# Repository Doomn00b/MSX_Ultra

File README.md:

# MSX_Ultra
 MSX2+ compatible Mini-ITX computer system, inspired by Sergey Kiselev's Omega Home Computer.

 This project is an open source implementation, and extension, of an MSX2+ compatible computer. The project is modular, and is built using a combination of 1980's-1990's era components - Z380 CPU, V9958 VDP, YM2610 PSG/FM-generator, and some newer components, such as 512 KiB SRAM and 512 KiB Flash ROM and dual FPGA's for the MSX-engine/Chipset (AT40K FPGAs).

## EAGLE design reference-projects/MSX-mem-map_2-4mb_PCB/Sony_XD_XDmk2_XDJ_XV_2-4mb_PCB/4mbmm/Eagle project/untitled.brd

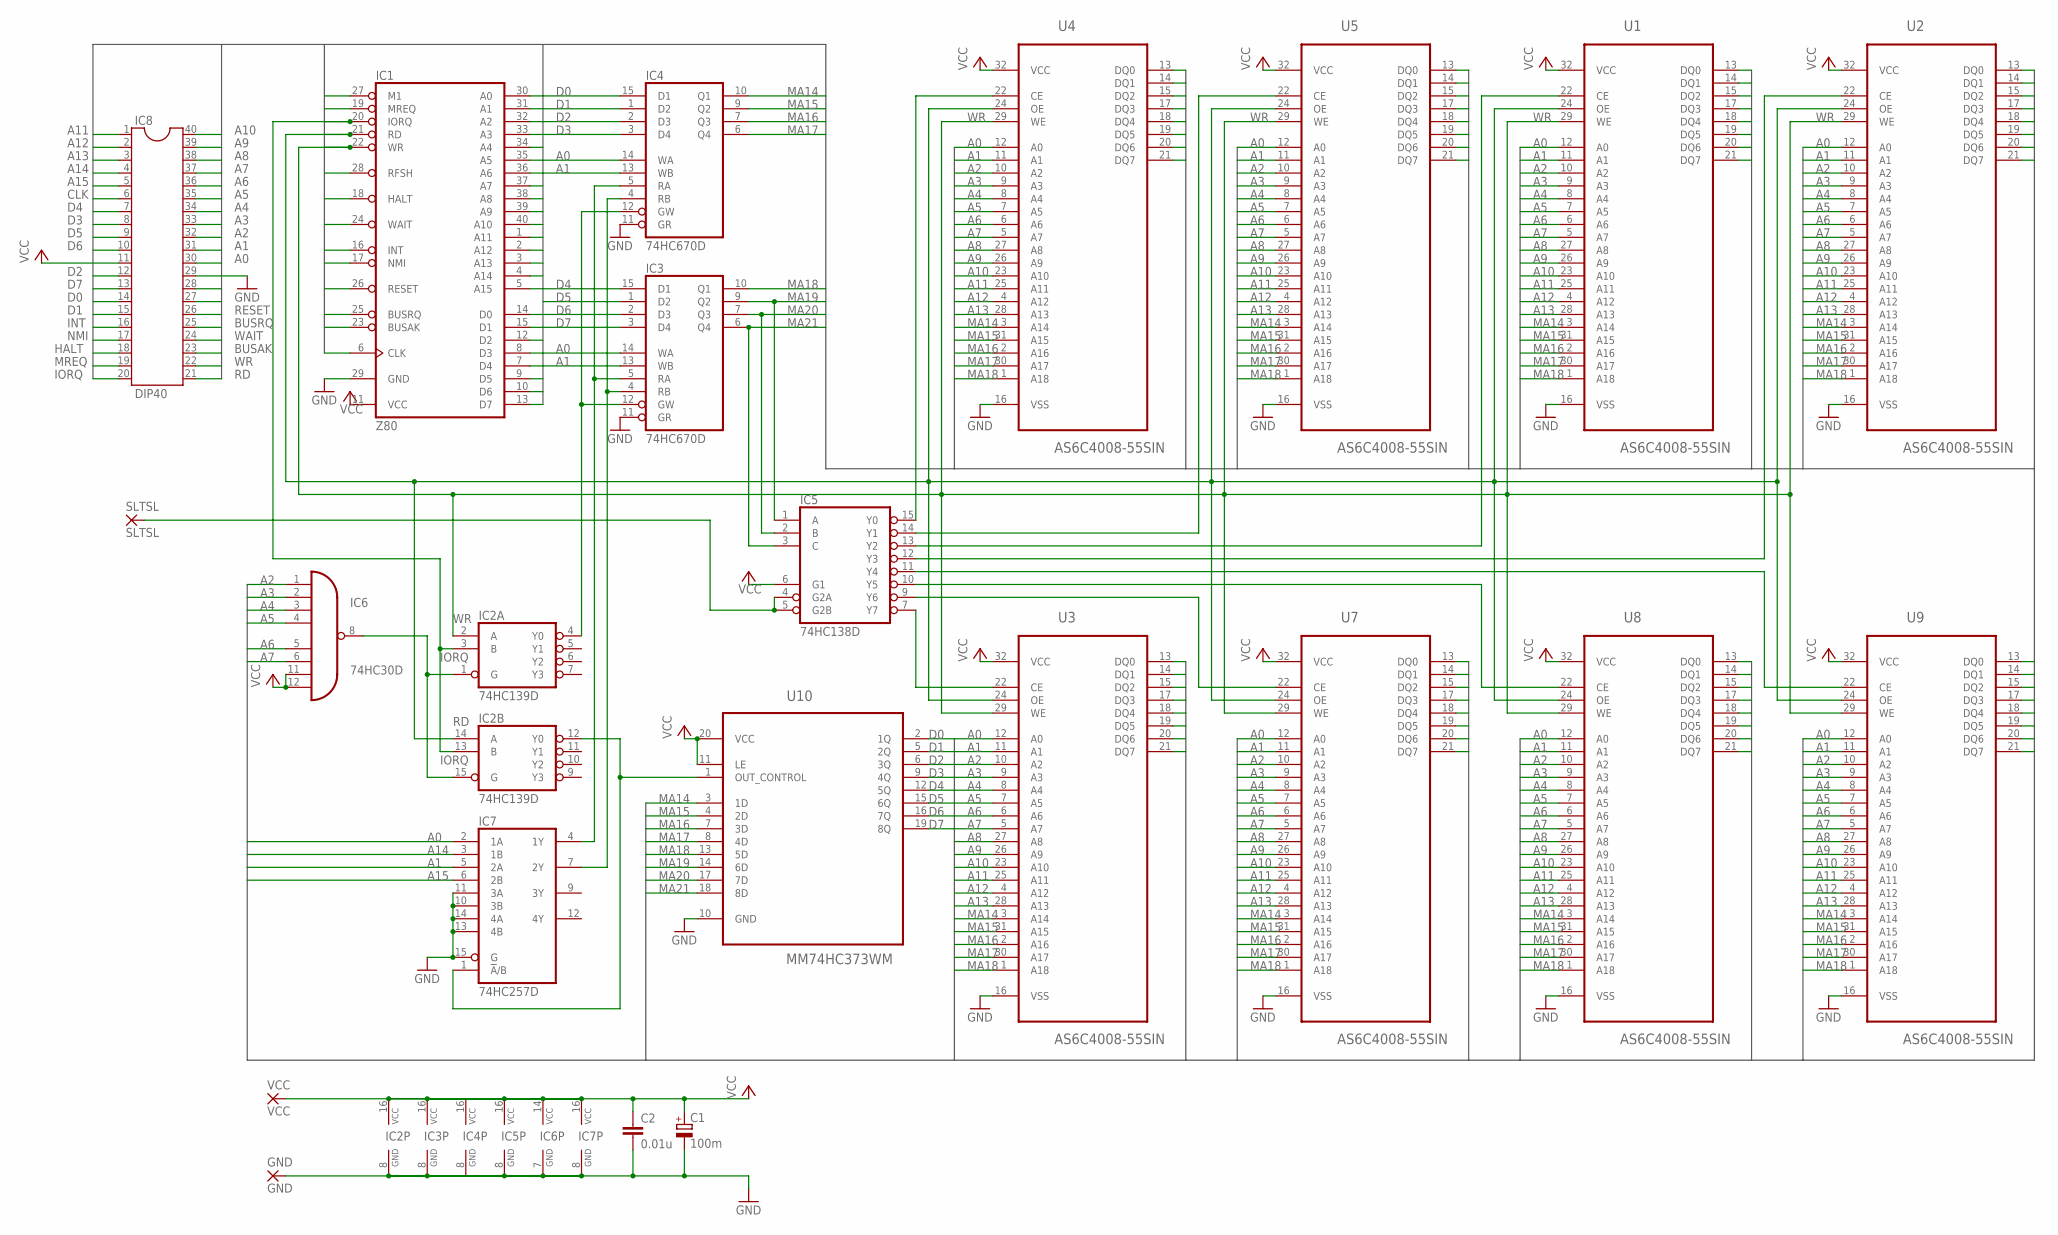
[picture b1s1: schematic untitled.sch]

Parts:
C1: 100m; E2,5-5
C2: 0.01u; C2.5-2
GND: GND; 1,6/0,8
IC1: Z80; DIL40
IC2: 74HC139D; SO16
IC3, IC4: 74HC670D; SO16
IC5: 74HC138D; SO16
IC6: 74HC30D; SO14
IC7: 74HC257D; SO16
IC8: DIP40; DIL40
SLTSL: SLTSL; 1,6/0,8
U1, U2, U3, U4, U5, U7, U8, U9: AS6C4008-55SIN; SOIC127P1407X299-32N
U10: MM74HC373WM; SOIC127P1032X265-20N
VCC: VCC; 1,6/0,8

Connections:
A0: IC1.30 (A0), IC3.14 (WA), IC4.14 (WA), IC7.2 (1A), IC8.30, U1.12 (A0), U2.12 (A0), U3.12 (A0), U4.12 (A0), U5.12 (A0), U7.12 (A0), U8.12 (A0), U9.12 (A0)
A1: IC1.31 (A1), IC3.13 (WB), IC4.13 (WB), IC7.5 (2A), IC8.31, U1.11 (A1), U2.11 (A1), U3.11 (A1), U4.11 (A1), U5.11 (A1), U7.11 (A1), U8.11 (A1), U9.11 (A1)
A2: IC1.32 (A2), IC6.1 (I0), IC8.32, U1.10 (A2), U2.10 (A2), U3.10 (A2), U4.10 (A2), U5.10 (A2), U7.10 (A2), U8.10 (A2), U9.10 (A2)
A3: IC1.33 (A3), IC6.2 (I1), IC8.33, U1.9 (A3), U2.9 (A3), U3.9 (A3), U4.9 (A3), U5.9 (A3), U7.9 (A3), U8.9 (A3), U9.9 (A3)
A4: IC1.34 (A4), IC6.3 (I2), IC8.34, U1.8 (A4), U2.8 (A4), U3.8 (A4), U4.8 (A4), U5.8 (A4), U7.8 (A4), U8.8 (A4), U9.8 (A4)
A5: IC1.35 (A5), IC6.4 (I3), IC8.35, U1.7 (A5), U2.7 (A5), U3.7 (A5), U4.7 (A5), U5.7 (A5), U7.7 (A5), U8.7 (A5), U9.7 (A5)
A6: IC1.36 (A6), IC6.5 (I4), IC8.36, U1.6 (A6), U2.6 (A6), U3.6 (A6), U4.6 (A6), U5.6 (A6), U7.6 (A6), U8.6 (A6), U9.6 (A6)
A7: IC1.37 (A7), IC6.6 (I5), IC8.37, U1.5 (A7), U2.5 (A7), U3.5 (A7), U4.5 (A7), U5.5 (A7), U7.5 (A7), U8.5 (A7), U9.5 (A7)
A8: IC1.38 (A8), IC8.38, U1.27 (A8), U2.27 (A8), U3.27 (A8), U4.27 (A8), U5.27 (A8), U7.27 (A8), U8.27 (A8), U9.27 (A8)
A9: IC1.39 (A9), IC8.39, U1.26 (A9), U2.26 (A9), U3.26 (A9), U4.26 (A9), U5.26 (A9), U7.26 (A9), U8.26 (A9), U9.26 (A9)
A10: IC1.40 (A10), IC8.40, U1.23 (A10), U2.23 (A10), U3.23 (A10), U4.23 (A10), U5.23 (A10), U7.23 (A10), U8.23 (A10), U9.23 (A10)
A11: IC1.1 (A11), IC8.1, U1.25 (A11), U2.25 (A11), U3.25 (A11), U4.25 (A11), U5.25 (A11), U7.25 (A11), U8.25 (A11), U9.25 (A11)
A12: IC1.2 (A12), IC8.2, U1.4 (A12), U2.4 (A12), U3.4 (A12), U4.4 (A12), U5.4 (A12), U7.4 (A12), U8.4 (A12), U9.4 (A12)
A13: IC1.3 (A13), IC8.3, U1.28 (A13), U2.28 (A13), U3.28 (A13), U4.28 (A13), U5.28 (A13), U7.28 (A13), U8.28 (A13), U9.28 (A13)
A14: IC1.4 (A14), IC7.3 (1B), IC8.4
A15: IC1.5 (A15), IC7.6 (2B), IC8.5
BUSAK: IC1.23 (BUSAK), IC8.23
BUSRQ: IC1.25 (BUSRQ), IC8.25
CLK: IC1.6 (CLK), IC8.6
D0: IC1.14 (D0), IC4.15 (D1), IC8.14, U1.13 (DQ0), U2.13 (DQ0), U3.13 (DQ0), U4.13 (DQ0), U5.13 (DQ0), U7.13 (DQ0), U8.13 (DQ0), U9.13 (DQ0), U10.2 (1Q)
D1: IC1.15 (D1), IC4.1 (D2), IC8.15, U1.14 (DQ1), U2.14 (DQ1), U3.14 (DQ1), U4.14 (DQ1), U5.14 (DQ1), U7.14 (DQ1), U8.14 (DQ1), U9.14 (DQ1), U10.5 (2Q)
D2: IC1.12 (D2), IC4.2 (D3), IC8.12, U1.15 (DQ2), U2.15 (DQ2), U3.15 (DQ2), U4.15 (DQ2), U5.15 (DQ2), U7.15 (DQ2), U8.15 (DQ2), U9.15 (DQ2), U10.6 (3Q)
D3: IC1.8 (D3), IC4.3 (D4), IC8.8, U1.17 (DQ3), U2.17 (DQ3), U3.17 (DQ3), U4.17 (DQ3), U5.17 (DQ3), U7.17 (DQ3), U8.17 (DQ3), U9.17 (DQ3), U10.9 (4Q)
D4: IC1.7 (D4), IC3.15 (D1), IC8.7, U1.18 (DQ4), U2.18 (DQ4), U3.18 (DQ4), U4.18 (DQ4), U5.18 (DQ4), U7.18 (DQ4), U8.18 (DQ4), U9.18 (DQ4), U10.12 (5Q)
D5: IC1.9 (D5), IC3.1 (D2), IC8.9, U1.19 (DQ5), U2.19 (DQ5), U3.19 (DQ5), U4.19 (DQ5), U5.19 (DQ5), U7.19 (DQ5), U8.19 (DQ5), U9.19 (DQ5), U10.15 (6Q)
D6: IC1.10 (D6), IC3.2 (D3), IC8.10, U1.20 (DQ6), U2.20 (DQ6), U3.20 (DQ6), U4.20 (DQ6), U5.20 (DQ6), U7.20 (DQ6), U8.20 (DQ6), U9.20 (DQ6), U10.16 (7Q)
D7: IC1.13 (D7), IC3.3 (D4), IC8.13, U1.21 (DQ7), U2.21 (DQ7), U3.21 (DQ7), U4.21 (DQ7), U5.21 (DQ7), U7.21 (DQ7), U8.21 (DQ7), U9.21 (DQ7), U10.19 (8Q)
GND: C1.-, C2.2, GND.1, IC1.29 (GND), IC2.8 (GND), IC3.8 (GND), IC3.11 (GR), IC4.8 (GND), IC4.11 (GR), IC5.8 (GND), IC6.7 (GND), IC7.8 (GND), IC7.10 (3B), IC7.11 (3A), IC7.13 (4B), IC7.14 (4A), IC7.15 (G), IC8.29, U1.16 (VSS), U2.16 (VSS), U3.16 (VSS), U4.16 (VSS), U5.16 (VSS), U7.16 (VSS), U8.16 (VSS), U9.16 (VSS), U10.10 (GND)
HALT: IC1.18 (HALT), IC8.18
INT: IC1.16 (INT), IC8.16
IORQ: IC1.20 (IORQ), IC2.3 (B), IC2.13 (B), IC8.20
M1: IC1.27 (M1), IC8.27
MA14: IC4.10 (Q1), U1.3 (A14), U2.3 (A14), U3.3 (A14), U4.3 (A14), U5.3 (A14), U7.3 (A14), U8.3 (A14), U9.3 (A14), U10.3 (1D)
MA15: IC4.9 (Q2), U1.31 (A15), U2.31 (A15), U3.31 (A15), U4.31 (A15), U5.31 (A15), U7.31 (A15), U8.31 (A15), U9.31 (A15), U10.4 (2D)
MA16: IC4.7 (Q3), U1.2 (A16), U2.2 (A16), U3.2 (A16), U4.2 (A16), U5.2 (A16), U7.2 (A16), U8.2 (A16), U9.2 (A16), U10.7 (3D)
MA17: IC4.6 (Q4), U1.30 (A17), U2.30 (A17), U3.30 (A17), U4.30 (A17), U5.30 (A17), U7.30 (A17), U8.30 (A17), U9.30 (A17), U10.8 (4D)
MA18: IC3.10 (Q1), U1.1 (A18), U2.1 (A18), U3.1 (A18), U4.1 (A18), U5.1 (A18), U7.1 (A18), U8.1 (A18), U9.1 (A18), U10.13 (5D)
MA19: IC3.9 (Q2), IC5.1 (A), U10.14 (6D)
MA20: IC3.7 (Q3), IC5.2 (B), U10.17 (7D)
MA21: IC3.6 (Q4), IC5.3 (C), U10.18 (8D)
MREQ: IC1.19 (MREQ), IC8.19
unnamed: IC2.12 (Y0), IC7.1 (!A!/B), U10.1 (OUT_CONTROL)
unnamed: IC5.13 (Y2), U1.22 (CE)
unnamed: IC5.12 (Y3), U2.22 (CE)
unnamed: IC3.5 (RA), IC4.5 (RA), IC7.4 (1Y)
unnamed: IC5.15 (Y0), U4.22 (CE)
unnamed: IC5.14 (Y1), U5.22 (CE)
unnamed: IC3.4 (RB), IC4.4 (RB), IC7.7 (2Y)
unnamed: IC5.11 (Y4), U9.22 (CE)
unnamed: IC2.1 (G), IC2.15 (G), IC6.8 (O)
unnamed: IC5.10 (Y5), U8.22 (CE)
unnamed: IC5.9 (Y6), U7.22 (CE)
unnamed: IC2.4 (Y0), IC3.12 (GW), IC4.12 (GW)
unnamed: IC5.4 (G2A), IC5.5 (G2B), SLTSL.1
unnamed: IC5.7 (Y7), U3.22 (CE)
NMI: IC1.17 (NMI), IC8.17
RD: IC1.21 (RD), IC2.14 (A), IC8.21, U1.24 (OE), U2.24 (OE), U3.24 (OE), U4.24 (OE), U5.24 (OE), U7.24 (OE), U8.24 (OE), U9.24 (OE)
RESET: IC1.26 (RESET), IC8.26
RFSH: IC1.28 (RFSH), IC8.28
VCC: C1.+, C2.1, IC1.11 (VCC), IC2.16 (VCC), IC3.16 (VCC), IC4.16 (VCC), IC5.6 (G1), IC5.16 (VCC), IC6.11 (I6), IC6.12 (I7), IC6.14 (VCC), IC7.16 (VCC), IC8.11, U1.32 (VCC), U2.32 (VCC), U3.32 (VCC), U4.32 (VCC), U5.32 (VCC), U7.32 (VCC), U8.32 (VCC), U9.32 (VCC), U10.11 (LE), U10.20 (VCC), VCC.1
WAIT: IC1.24 (WAIT), IC8.24
WR: IC1.22 (WR), IC2.2 (A), IC8.22, U1.29 (WE), U2.29 (WE), U3.29 (WE), U4.29 (WE), U5.29 (WE), U7.29 (WE), U8.29 (WE), U9.29 (WE)

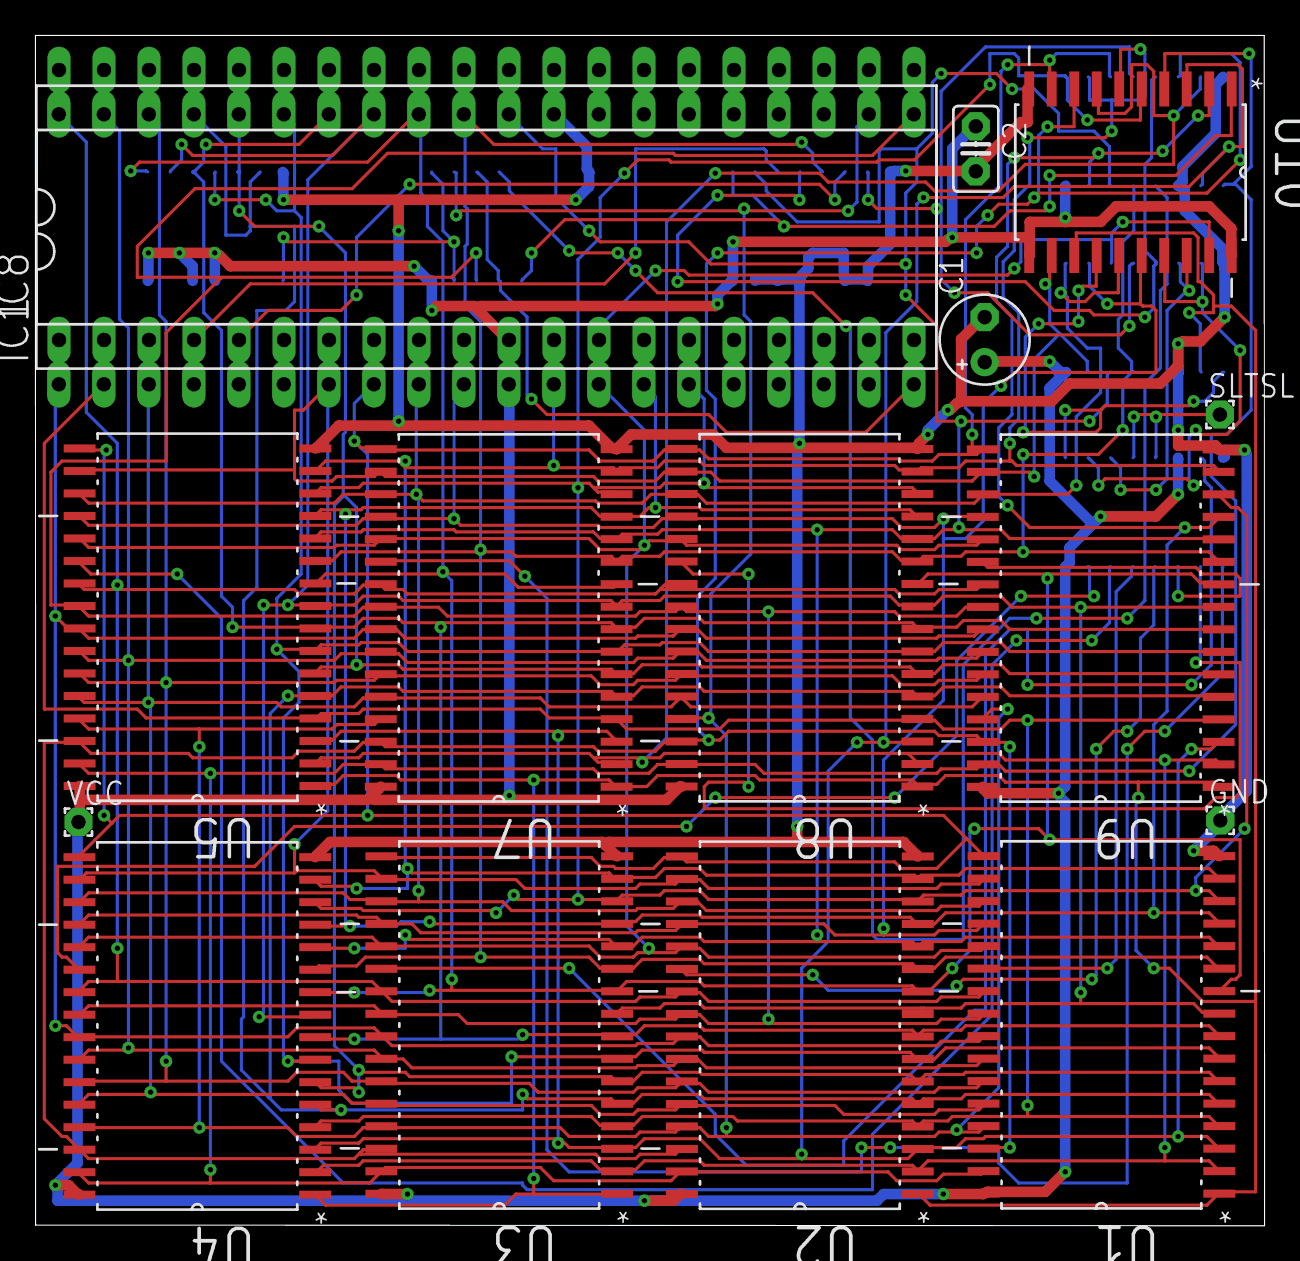
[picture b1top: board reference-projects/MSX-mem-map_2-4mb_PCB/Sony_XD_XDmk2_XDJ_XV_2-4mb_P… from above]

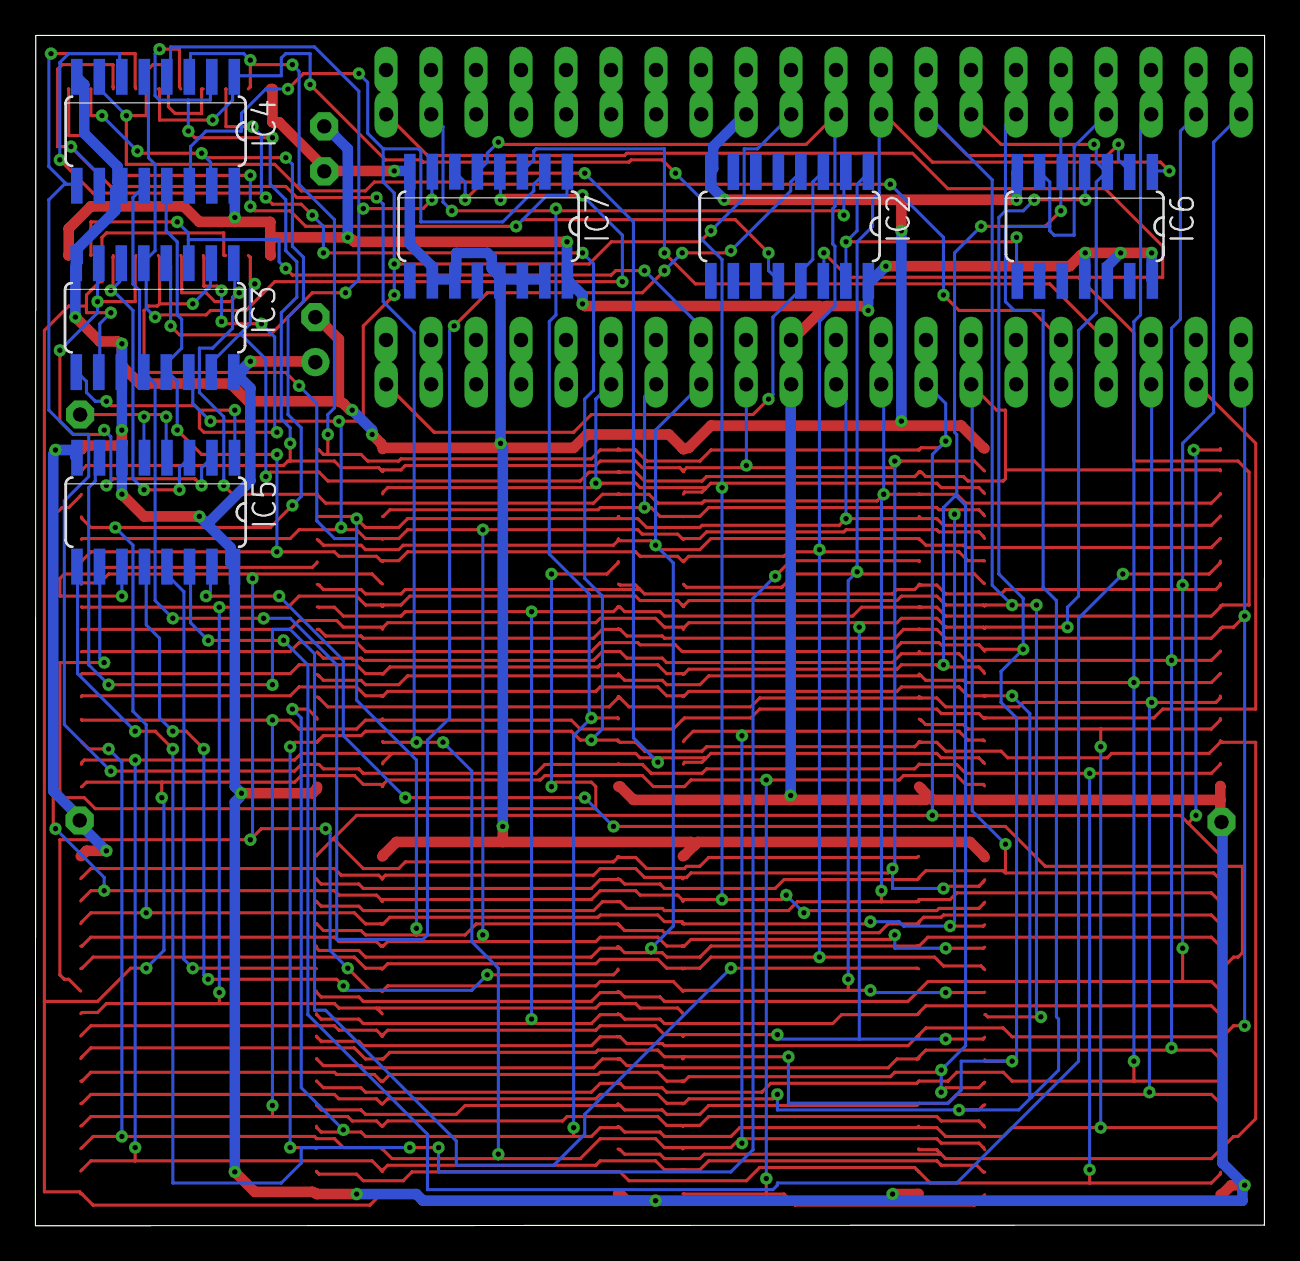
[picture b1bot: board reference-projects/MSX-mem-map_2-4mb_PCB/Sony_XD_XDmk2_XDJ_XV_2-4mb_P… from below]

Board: 2 copper layers, 69.4 x 67.2 mm, 22 parts (6 on the bottom side), 62 nets.

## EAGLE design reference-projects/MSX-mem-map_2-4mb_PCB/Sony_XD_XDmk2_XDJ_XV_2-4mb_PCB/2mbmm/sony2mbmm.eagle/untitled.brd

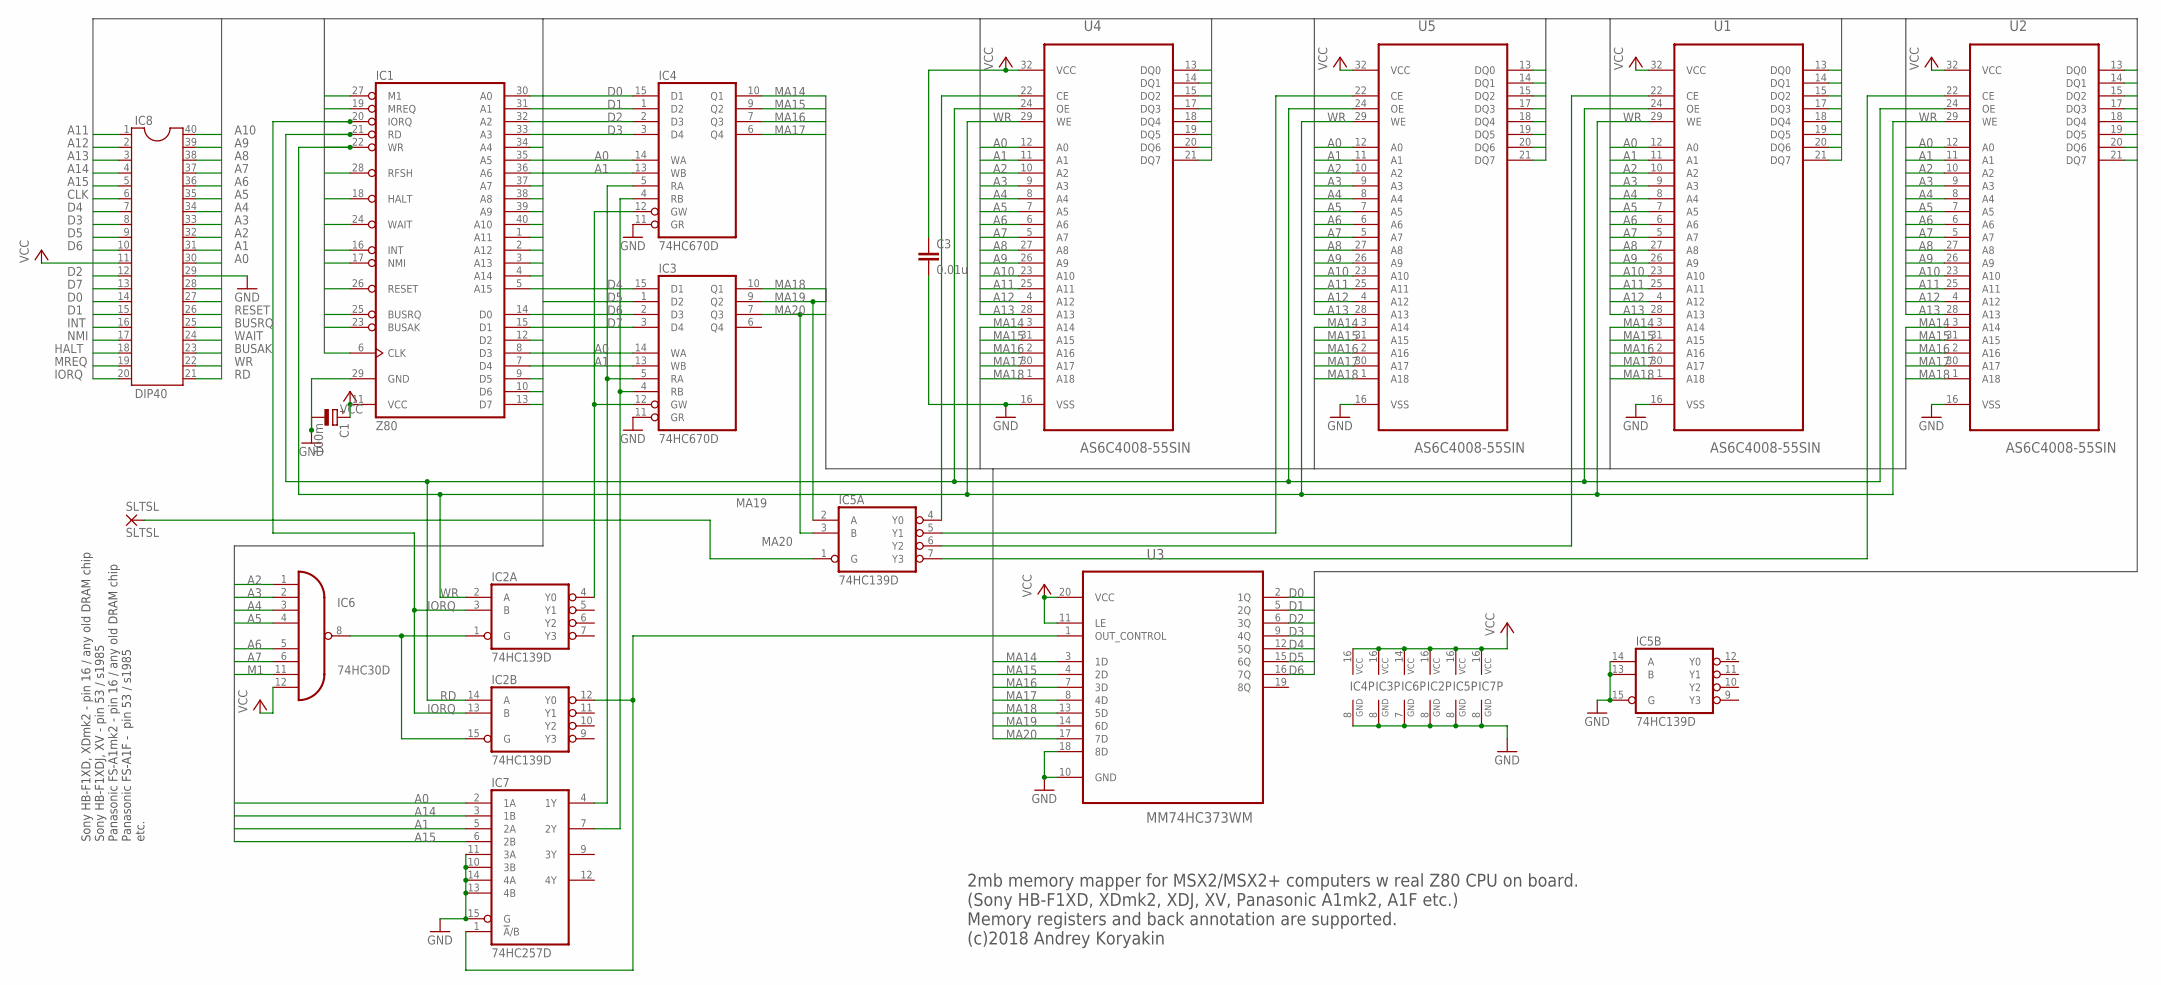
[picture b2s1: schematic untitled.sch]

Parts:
C1: 100m; E2,5-5
C3: 0.01u; C2.5-2
IC1: Z80; DIL40
IC2, IC5: 74HC139D; SO16
IC3, IC4: 74HC670D; SO16
IC6: 74HC30D; SO14
IC7: 74HC257D; SO16
IC8: DIP40; DIL40
SLTSL: SLTSL; 1,6/0,8
U1, U2, U4, U5: AS6C4008-55SIN; SOIC127P1407X299-32N
U3: MM74HC373WM; SOIC127P1032X265-20N

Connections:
A0: IC1.30 (A0), IC3.14 (WA), IC4.14 (WA), IC7.2 (1A), IC8.30, U1.12 (A0), U2.12 (A0), U4.12 (A0), U5.12 (A0)
A1: IC1.31 (A1), IC3.13 (WB), IC4.13 (WB), IC7.5 (2A), IC8.31, U1.11 (A1), U2.11 (A1), U4.11 (A1), U5.11 (A1)
A2: IC1.32 (A2), IC6.1 (I0), IC8.32, U1.10 (A2), U2.10 (A2), U4.10 (A2), U5.10 (A2)
A3: IC1.33 (A3), IC6.2 (I1), IC8.33, U1.9 (A3), U2.9 (A3), U4.9 (A3), U5.9 (A3)
A4: IC1.34 (A4), IC6.3 (I2), IC8.34, U1.8 (A4), U2.8 (A4), U4.8 (A4), U5.8 (A4)
A5: IC1.35 (A5), IC6.4 (I3), IC8.35, U1.7 (A5), U2.7 (A5), U4.7 (A5), U5.7 (A5)
A6: IC1.36 (A6), IC6.5 (I4), IC8.36, U1.6 (A6), U2.6 (A6), U4.6 (A6), U5.6 (A6)
A7: IC1.37 (A7), IC6.6 (I5), IC8.37, U1.5 (A7), U2.5 (A7), U4.5 (A7), U5.5 (A7)
A8: IC1.38 (A8), IC8.38, U1.27 (A8), U2.27 (A8), U4.27 (A8), U5.27 (A8)
A9: IC1.39 (A9), IC8.39, U1.26 (A9), U2.26 (A9), U4.26 (A9), U5.26 (A9)
A10: IC1.40 (A10), IC8.40, U1.23 (A10), U2.23 (A10), U4.23 (A10), U5.23 (A10)
A11: IC1.1 (A11), IC8.1, U1.25 (A11), U2.25 (A11), U4.25 (A11), U5.25 (A11)
A12: IC1.2 (A12), IC8.2, U1.4 (A12), U2.4 (A12), U4.4 (A12), U5.4 (A12)
A13: IC1.3 (A13), IC8.3, U1.28 (A13), U2.28 (A13), U4.28 (A13), U5.28 (A13)
A14: IC1.4 (A14), IC7.3 (1B), IC8.4
A15: IC1.5 (A15), IC7.6 (2B), IC8.5
BUSAK: IC1.23 (BUSAK), IC8.23
BUSRQ: IC1.25 (BUSRQ), IC8.25
CLK: IC1.6 (CLK), IC8.6
D0: IC1.14 (D0), IC4.15 (D1), IC8.14, U1.13 (DQ0), U2.13 (DQ0), U3.2 (1Q), U4.13 (DQ0), U5.13 (DQ0)
D1: IC1.15 (D1), IC4.1 (D2), IC8.15, U1.14 (DQ1), U2.14 (DQ1), U3.5 (2Q), U4.14 (DQ1), U5.14 (DQ1)
D2: IC1.12 (D2), IC4.2 (D3), IC8.12, U1.15 (DQ2), U2.15 (DQ2), U3.6 (3Q), U4.15 (DQ2), U5.15 (DQ2)
D3: IC1.8 (D3), IC4.3 (D4), IC8.8, U1.17 (DQ3), U2.17 (DQ3), U3.9 (4Q), U4.17 (DQ3), U5.17 (DQ3)
D4: IC1.7 (D4), IC3.15 (D1), IC8.7, U1.18 (DQ4), U2.18 (DQ4), U3.12 (5Q), U4.18 (DQ4), U5.18 (DQ4)
D5: IC1.9 (D5), IC3.1 (D2), IC8.9, U1.19 (DQ5), U2.19 (DQ5), U3.15 (6Q), U4.19 (DQ5), U5.19 (DQ5)
D6: IC1.10 (D6), IC3.2 (D3), IC8.10, U1.20 (DQ6), U2.20 (DQ6), U3.16 (7Q), U4.20 (DQ6), U5.20 (DQ6)
D7: IC1.13 (D7), IC3.3 (D4), IC8.13, U1.21 (DQ7), U2.21 (DQ7), U4.21 (DQ7), U5.21 (DQ7)
GND: C1.-, C3.2, IC1.29 (GND), IC2.8 (GND), IC3.8 (GND), IC3.11 (GR), IC4.8 (GND), IC4.11 (GR), IC5.8 (GND), IC5.13 (B), IC5.14 (A), IC5.15 (G), IC6.7 (GND), IC7.8 (GND), IC7.10 (3B), IC7.11 (3A), IC7.13 (4B), IC7.14 (4A), IC7.15 (G), IC8.29, U1.16 (VSS), U2.16 (VSS), U3.10 (GND), U3.18 (8D), U4.16 (VSS), U5.16 (VSS)
HALT: IC1.18 (HALT), IC8.18
INT: IC1.16 (INT), IC8.16
IORQ: IC1.20 (IORQ), IC2.3 (B), IC2.13 (B), IC8.20
M1: IC1.27 (M1), IC6.11 (I6), IC8.27
MA14: IC4.10 (Q1), U1.3 (A14), U2.3 (A14), U3.3 (1D), U4.3 (A14), U5.3 (A14)
MA15: IC4.9 (Q2), U1.31 (A15), U2.31 (A15), U3.4 (2D), U4.31 (A15), U5.31 (A15)
MA16: IC4.7 (Q3), U1.2 (A16), U2.2 (A16), U3.7 (3D), U4.2 (A16), U5.2 (A16)
MA17: IC4.6 (Q4), U1.30 (A17), U2.30 (A17), U3.8 (4D), U4.30 (A17), U5.30 (A17)
MA18: IC3.10 (Q1), U1.1 (A18), U2.1 (A18), U3.13 (5D), U4.1 (A18), U5.1 (A18)
MA19: IC3.9 (Q2), IC5.2 (A), U3.14 (6D)
MA20: IC3.7 (Q3), IC5.3 (B), U3.17 (7D)
MREQ: IC1.19 (MREQ), IC8.19
unnamed: IC2.12 (Y0), IC7.1 (!A!/B), U3.1 (OUT_CONTROL)
unnamed: IC5.6 (Y2), U1.22 (CE)
unnamed: IC5.7 (Y3), U2.22 (CE)
unnamed: IC3.5 (RA), IC4.5 (RA), IC7.4 (1Y)
unnamed: IC5.4 (Y0), U4.22 (CE)
unnamed: IC5.5 (Y1), U5.22 (CE)
unnamed: IC3.4 (RB), IC4.4 (RB), IC7.7 (2Y)
unnamed: IC2.1 (G), IC2.15 (G), IC6.8 (O)
unnamed: IC2.4 (Y0), IC3.12 (GW), IC4.12 (GW)
unnamed: IC5.1 (G), SLTSL.1
NMI: IC1.17 (NMI), IC8.17
RD: IC1.21 (RD), IC2.14 (A), IC8.21, U1.24 (OE), U2.24 (OE), U4.24 (OE), U5.24 (OE)
RESET: IC1.26 (RESET), IC8.26
RFSH: IC1.28 (RFSH), IC8.28
VCC: C1.+, C3.1, IC1.11 (VCC), IC2.16 (VCC), IC3.16 (VCC), IC4.16 (VCC), IC5.16 (VCC), IC6.12 (I7), IC6.14 (VCC), IC7.16 (VCC), IC8.11, U1.32 (VCC), U2.32 (VCC), U3.11 (LE), U3.20 (VCC), U4.32 (VCC), U5.32 (VCC)
WAIT: IC1.24 (WAIT), IC8.24
WR: IC1.22 (WR), IC2.2 (A), IC8.22, U1.29 (WE), U2.29 (WE), U4.29 (WE), U5.29 (WE)

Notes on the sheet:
2mb memory mapper for MSX2/MSX2+ computers w real Z80 CPU on board. (Sony HB-F1XD, XDmk2, XDJ, XV, Panasonic A1mk2, A1F etc.) Memory registers and back annotation are supported. (c)2018 Andrey Koryakin
Sony HB-F1XD, XDmk2 - pin 16 / any old DRAM chip Sony HB-F1XDJ, XV - pin 53 / s1985 Panasonic FS-A1mk2 - pin 16 / any old DRAM chip Panasonic FS-A1F - pin 53 / s1985 etc.

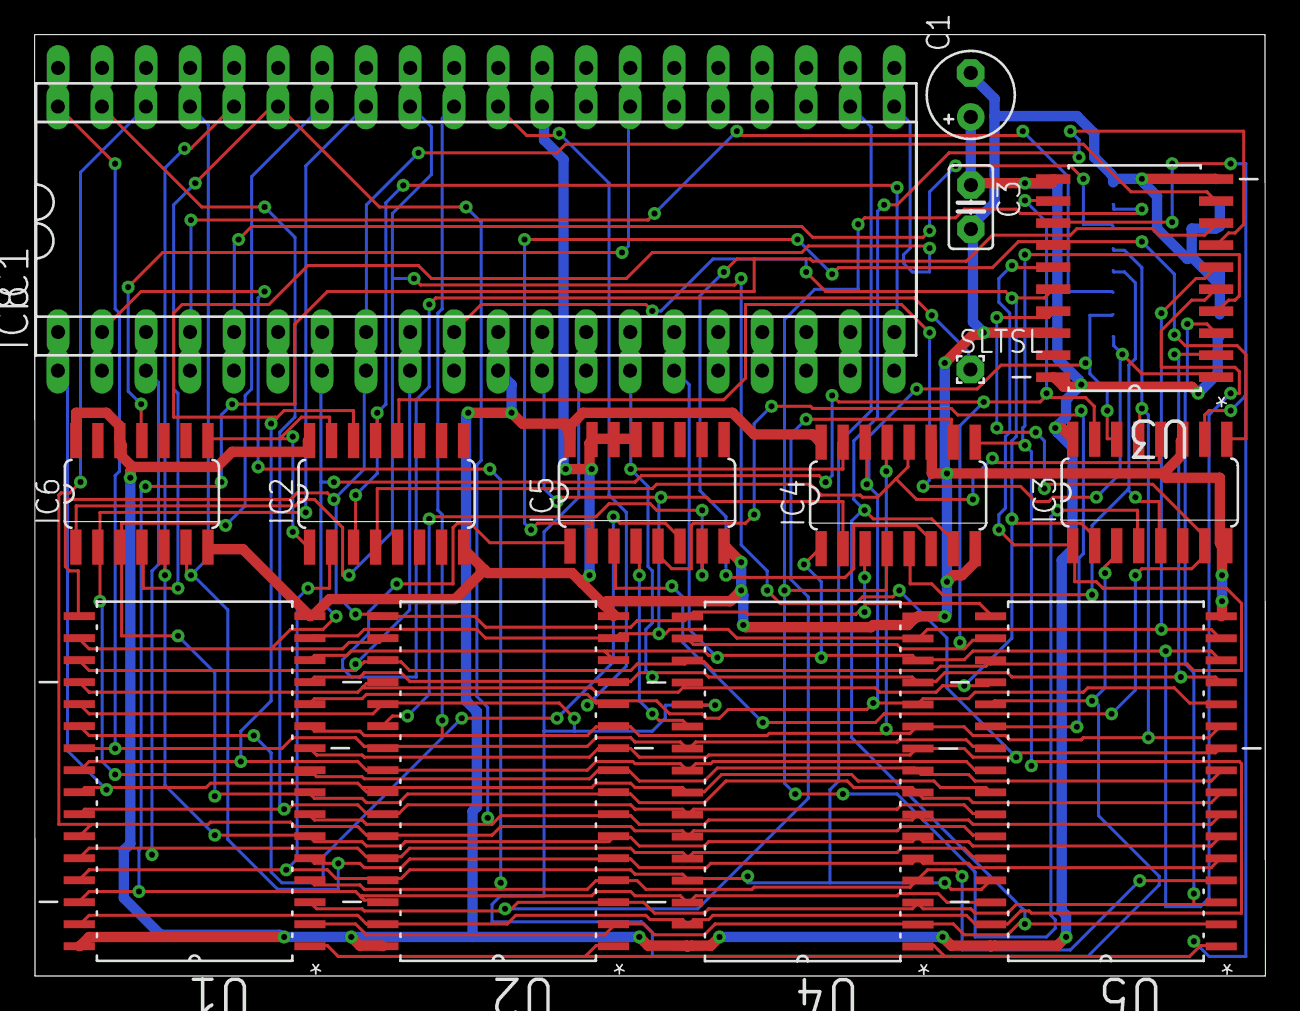
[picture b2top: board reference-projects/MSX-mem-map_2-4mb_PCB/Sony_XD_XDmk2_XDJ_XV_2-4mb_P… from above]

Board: 2 copper layers, 71.0 x 54.3 mm, 16 parts (1 on the bottom side), 57 nets.

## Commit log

2022-05-06 Initial commit.
    Setting up folder-structure, and uploading the currently achieved progress.
2022-05-29 Routed the VDP-board further, as well as making it a 4-layer board - also added an exception in the gitignore, for big images.
2022-06-10 Finished the VDP-board, finished up the mixer-section, removed the buffer-pins from the FPGA, and instead added external buffers for the slots, designed a marquee-block with the Ultra-MSX logo, desig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
2022-06-11 Started routing the Cassette-player on the PCB.
2022-06-26 Added SD-card slot, made basic 3d-model for sd-card slot, connected it up in the schematic, and numerous other tweaks.
2022-07-19 Redesigned VDP-board to include a socket, increased it to 4 layers. Various clean-ups here and there. Improved the printer-port and joystick-port 3D-models. Improved the cooling-fin 3D-model, and add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
2022-07-19 Generated first PDF-files
2022-08-05 Reworked the Printer-port 3D model, and the Scart 3D-model. Generated a 3D model of the main board. Moved peripheral components from separate expansion-headers, to a singular IO-shield board.
2022-08-11 Redesigning of the IO-shield, to make room for Keyboard, power and USB.
2022-08-28 Started remodelling the MSX cart-shells, as they don't seem to fit the cartridge-pcb's. Bit of clean-up in the directories.
2022-09-12 slight bit of cleanup of folders and some work on 3D-models
2022-10-10 Multiple redesigns of the IO-shield. Replaced FPGA with lower pin-count AT10K, since the higher pin-count one is now obsolete.
2022-12-10 Added cooler and CPU-mount footprints, as well as Indication LEDs.
2023-04-27 Started fixing many small issues.
2023-10-12 Updated the readme, silenced multiple errors in Kicad regarding simulation-files.
2023-10-25 Added a 3D-model for the SDRAM-module. Prepping the design for a fork using a single, more modern FPGA.
2023-12-13 Many tweaks and changes, such as a slight redesign of the VDP-baord.
2023-12-13 Returned to Simm-72 memory module to simplify design, returned to AT40K40 with 254 io, FPGA.
